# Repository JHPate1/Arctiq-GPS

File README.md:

# Arctiq-GPS
A mainboard PCB design for my custom handheld navigation device.
(first time making a PCB and it all looks good so far!)

## What does it do?
This might seem vague if you don't know much about the project, so I'll try to explain everything here, along with who I am and my background.

## Who I am
I'm Jyot Patel, a 14-year-old living in the United States. I recently moved from Canada, where I was raised my entire life (born in India though). I like tinkering and making software projects in my free time, though I never really used GitHub that often. Git CLI just wasn't for me.

## What is this project?
This is the core foundation of my handheld device. It contains the power circuitry and the main GPS module that handles everything. At the heart of it sits an RPI CM4 module, which controls everything and runs the main OS I plan on flashing to the SD card.

## Why did I take on such an ambitious project for my first PCB?
Honestly, it was kind of a bad idea for a first PCB, but I do have experience with real hardware. It was more of a motivational thing: when you want to give up, you realize how much you've already put into the project, and that pushes you to keep going. This was my 4th revision of the board, so as you can see, it took me a while to get here.

## The routing looks ugly
I can admit the routing is terrible, but I checked it for the specific purpose and this will work just fine. I wasn't planning on making a Mona Lisa on a PCB. I just needed a functional board that won't explode after 3 years.

## Known Errors

Any DRC or ERC errors are left on purpose, KiCad was being a pain in the butt during import and export. I couldn't connect some traces, and there are a few schematic/footprint mixups. Take the PCB as the source of truth only!!!
If you spot anything else, feel free to open an issue.

### Special Thanks!
Special thanks to Hack Club Stardance for motivating me on this project. Without your help, I wouldn't have done it!

Thanks to https://github.com/ShawnHymel/rpi-cm4-carrier-template for providing me with the CM4 Carrier template!

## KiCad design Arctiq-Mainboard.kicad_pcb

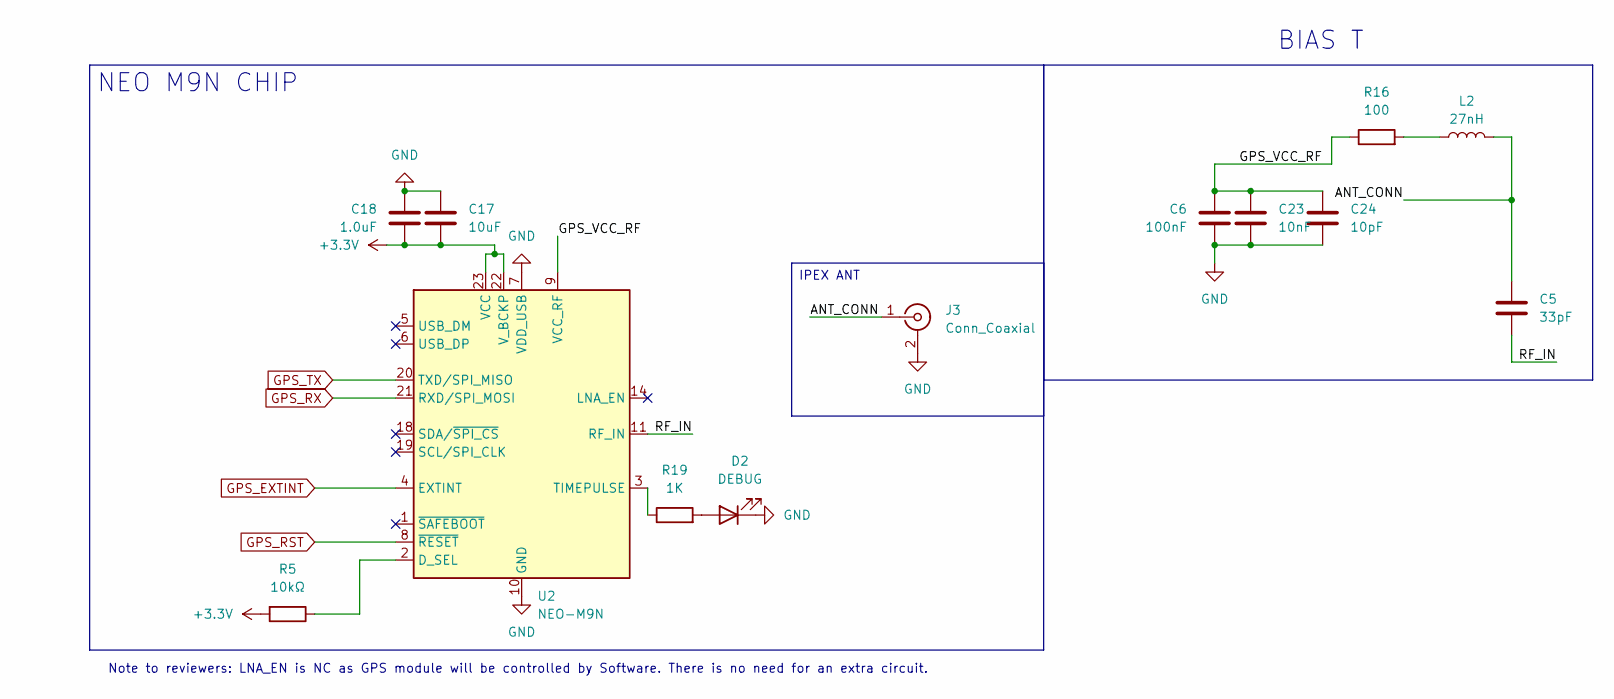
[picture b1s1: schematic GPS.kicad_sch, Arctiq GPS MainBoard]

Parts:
C5: 33pF; C_0603_1608Metric
C6: 100nF; C_0603_1608Metric
C17: 10uF; C_0603_1608Metric
C18: 1.0uF; C_0603_1608Metric
C23: 10nF; C_0603_1608Metric
C24: 10pF; C_0603_1608Metric
D2: DEBUG; LED_0402_1005Metric
J3: Conn_Coaxial; U.FL_Hirose_U.FL-R-SMT-1_Vertical
L2: 27nH; L_0402_1005Metric
R5: 10kΩ; R_0603_1608Metric
R16: 100; R_0603_1608Metric
R19: 1K; R_0603_1608Metric
U2: NEO-M9N; ublox_NEO

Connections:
+3.3V: C17.2, C18.2, R5.2, U2.22 (V_BCKP), U2.23 (VCC); also elsewhere on the board
/GPS Module/ANT_CONN: C5.2, J3.1 (In), L2.2
/GPS Module/GPS_VCC_RF: C6.2, C23.2, C24.2, R16.1, U2.9 (VCC_RF)
/GPS Module/RF_IN: C5.1, U2.11 (RF_IN)
GPS_EXTINT: U2.4 (EXTINT); also elsewhere on the board
GPS_RST: U2.8 (~RESET); also elsewhere on the board
GPS_RX: U2.21 (RXD/SPI_MOSI); also elsewhere on the board
GPS_TX: U2.20 (TXD/SPI_MISO); also elsewhere on the board
unnamed: D2.2 (A), R19.2
unnamed: L2.1, R16.2
unnamed: R5.1, U2.2 (D_SEL)
unnamed: R19.1, U2.3 (TIMEPULSE)

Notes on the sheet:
Note to reviewers: LNA_EN is NC as GPS module will be controlled by Software. There is no need for an extra circuit.
BIAS T
IPEX ANT
NEO M9N CHIP

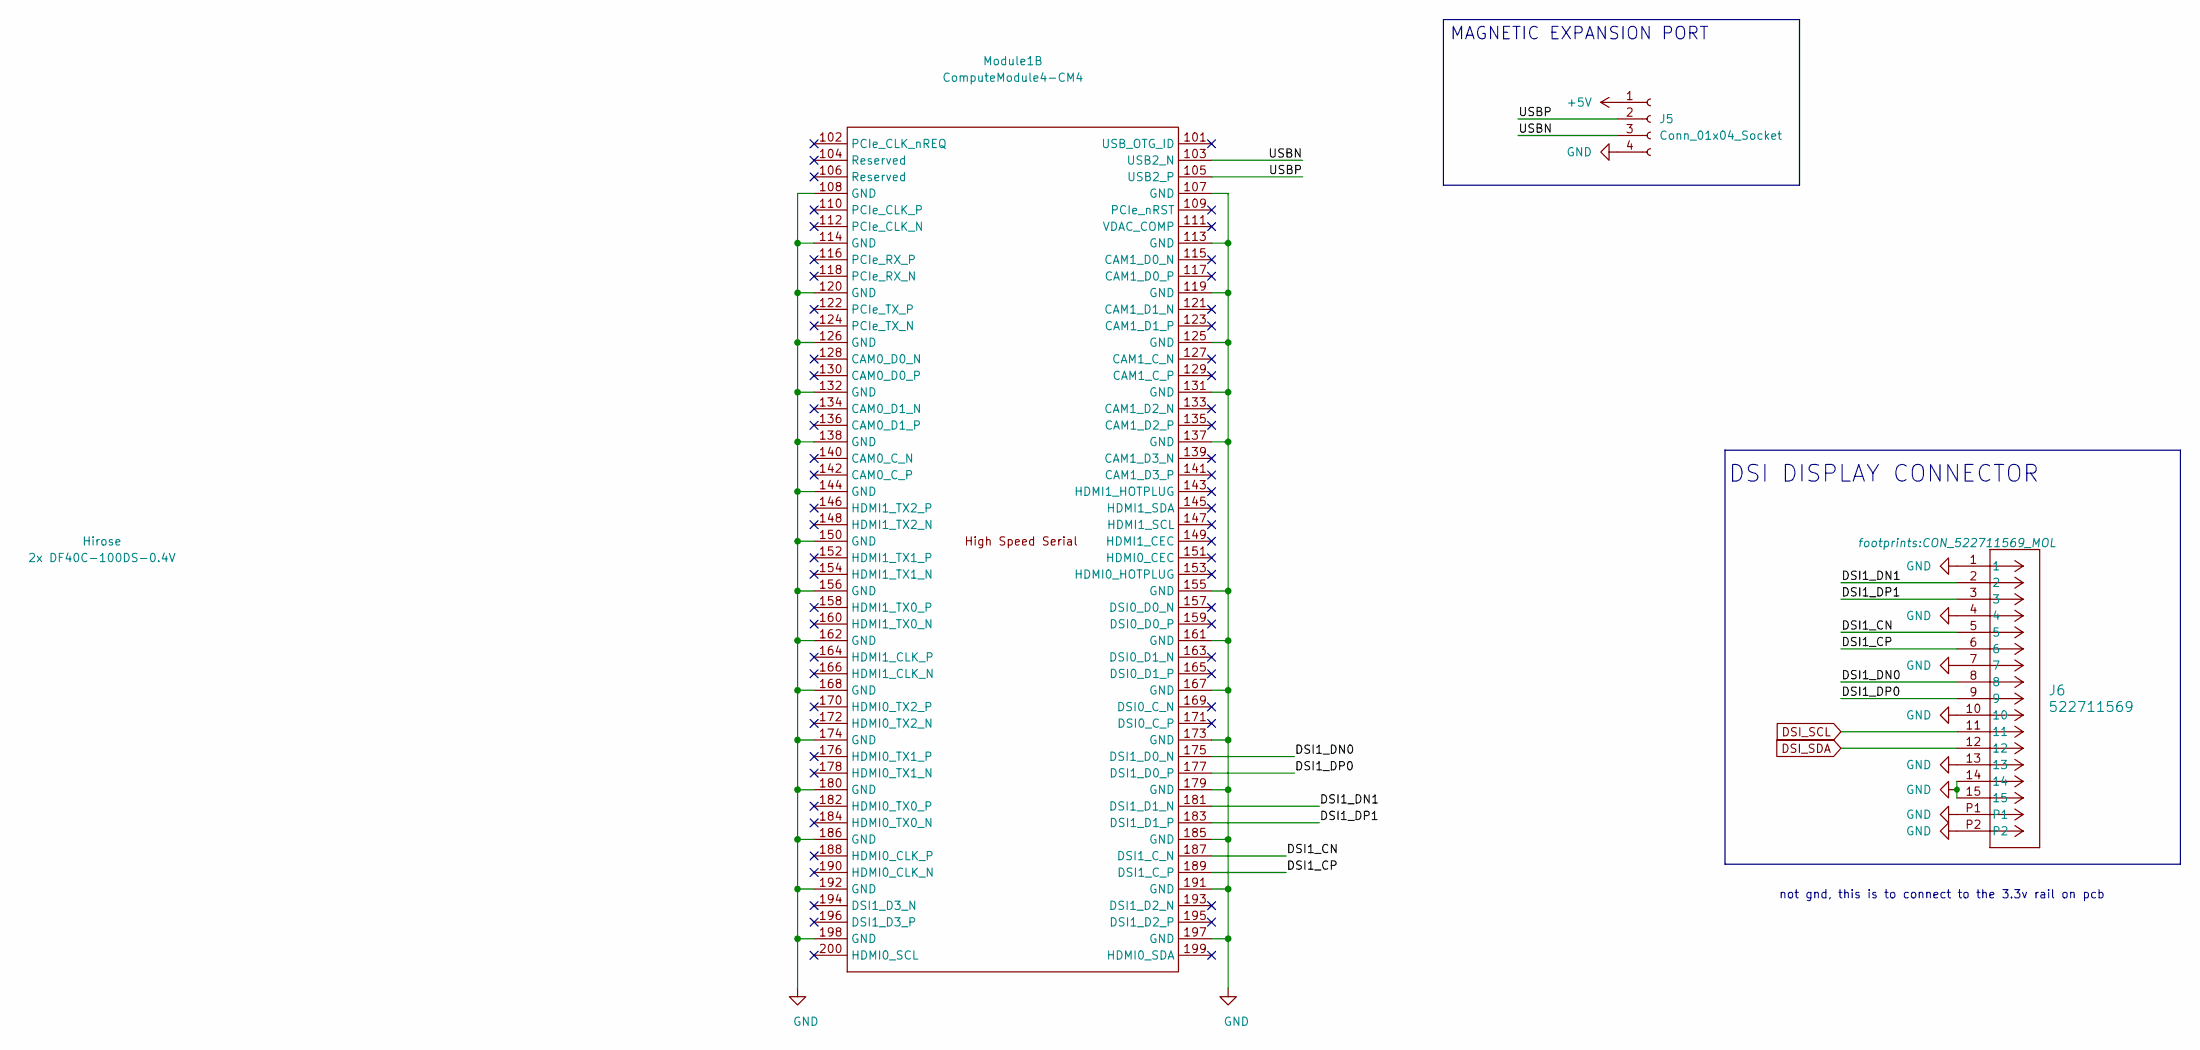
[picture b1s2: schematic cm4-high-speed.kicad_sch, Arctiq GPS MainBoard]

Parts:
J5: Conn_01x04_Socket; JST_NV_B04P-NV_1x04_P5.00mm_Vertical
J6: 522711569; CON_522711569_MOL
Module1: ComputeModule4-CM4; CONN100_DF40C-100DP-0.4V51_HIR; MPN 2x DF40C-100DS-0.4V; Digi-Key_PN 2x H11615CT-ND

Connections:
+5V: J5.1; also elsewhere on the board
/CM4 High Speed/DSI1_CN: J6.5, Module1.187 (DSI1_C_N)
/CM4 High Speed/DSI1_CP: J6.6, Module1.189 (DSI1_C_P)
/CM4 High Speed/DSI1_DN0: J6.8, Module1.175 (DSI1_D0_N)
/CM4 High Speed/DSI1_DN1: J6.2, Module1.181 (DSI1_D1_N)
/CM4 High Speed/DSI1_DP0: J6.9, Module1.177 (DSI1_D0_P)
/CM4 High Speed/DSI1_DP1: J6.3, Module1.183 (DSI1_D1_P)
/CM4 High Speed/USBN: J5.3, Module1.103 (USB2_N)
/CM4 High Speed/USBP: J5.2, Module1.105 (USB2_P)
DSI_SCL: J6.11; also elsewhere on the board
DSI_SDA: J6.12; also elsewhere on the board

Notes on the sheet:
not gnd, this is to connect to the 3.3v rail on pcb
DSI DISPLAY CONNECTOR
MAGNETIC EXPANSION PORT

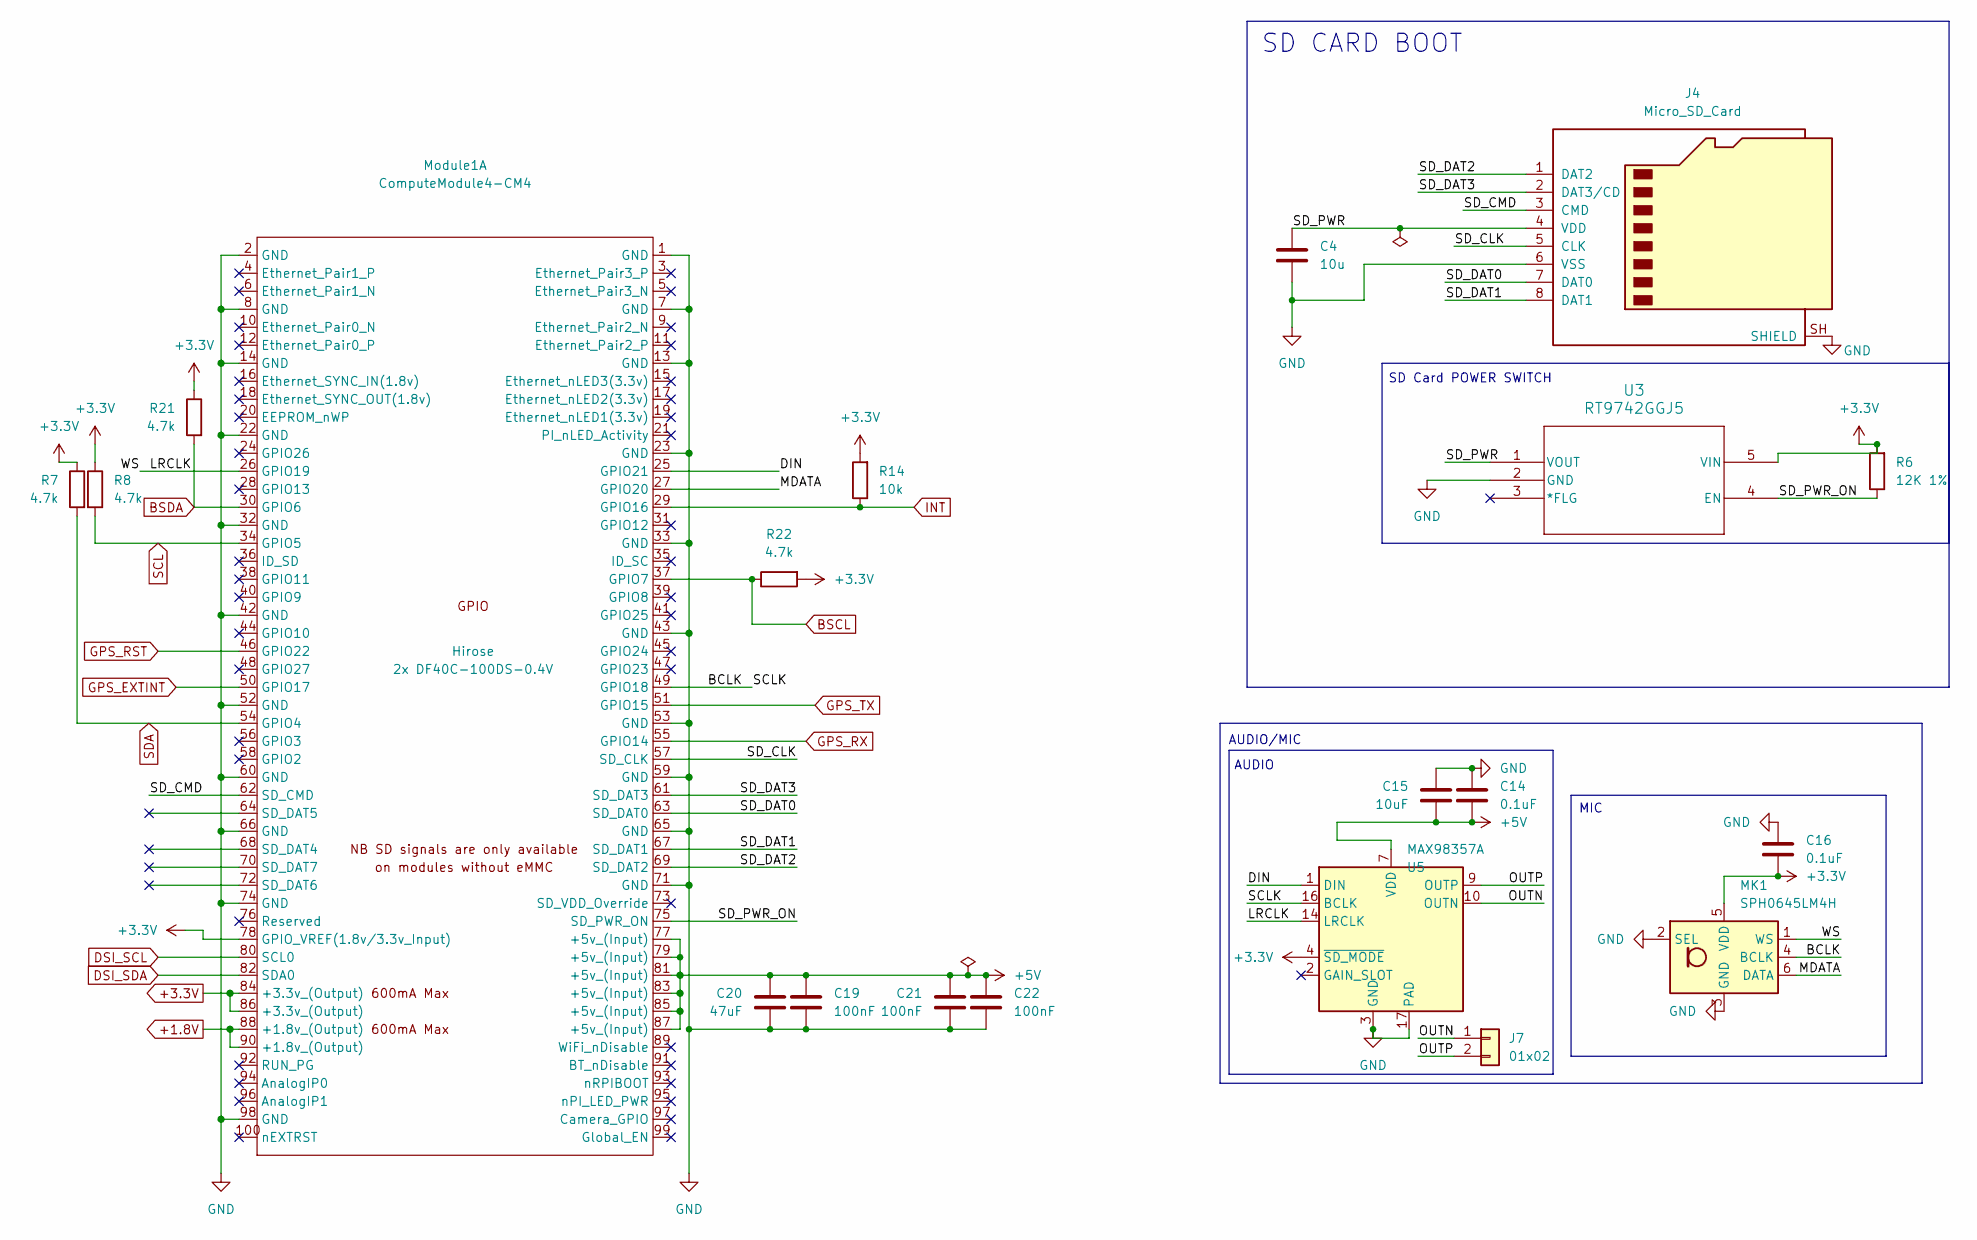
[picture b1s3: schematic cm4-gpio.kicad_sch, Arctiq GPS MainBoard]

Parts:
C4: 10u; C_0603_1608Metric
C14, C16: 0.1uF; C_0603_1608Metric
C15: 10uF; C_0603_1608Metric
C19, C21, C22: 100nF; C_0603_1608Metric
C20: 47uF; C_0603_1608Metric
J4: Micro_SD_Card; microSD_HC_Wuerth_693072010801
J7: 01x02; PinHeader_1x02_P2.54mm_Vertical
MK1: SPH0645LM4H; Knowles_SPH0645LM4H-6_3.5x2.65mm
Module1: ComputeModule4-CM4; CONN100_DF40C-100DP-0.4V51_HIR; MPN 2x DF40C-100DS-0.4V; Digi-Key_PN 2x H11615CT-ND
R6: 12K 1%; R_0603_1608Metric
R7, R8, R21, R22: 4.7k; R_0603_1608Metric
R14: 10k; R_0603_1608Metric
U3: RT9742GGJ5; TSOT-23-5_RIT
U5: MAX98357A; TQFN-16-1EP_3x3mm_P0.5mm_EP1.23x1.23mm

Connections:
+1.8V: Module1.88 (+1.8v_(Output)), Module1.90 (+1.8v_(Output))
+3.3V: C16.2, MK1.5 (VDD), Module1.78 (GPIO_VREF(1.8v/3.3v_Input)), Module1.84 (+3.3v_(Output)), Module1.86 (+3.3v_(Output)), R6.2, R7.1, R8.1, R14.2, R21.1, R22.2, U3.5 (VIN), U5.4 (~SD_MODE); also elsewhere on the board
+5V: C14.2, C15.2, C19.1, C20.2, C21.2, C22.1, Module1.77 (+5v_(Input)), Module1.79 (+5v_(Input)), Module1.81 (+5v_(Input)), Module1.83 (+5v_(Input)), Module1.85 (+5v_(Input)), Module1.87 (+5v_(Input)), U5.7 (VDD), U5.8 (VDD); also elsewhere on the board
/CM4 GPIO/BCLK: MK1.4 (BCLK), Module1.49 (GPIO18), U5.16 (BCLK)
/CM4 GPIO/DIN: Module1.25 (GPIO21), U5.1 (DIN)
/CM4 GPIO/LRCLK: MK1.1 (WS), Module1.26 (GPIO19), U5.14 (LRCLK)
/CM4 GPIO/MDATA: MK1.6 (DATA), Module1.27 (GPIO20)
/CM4 GPIO/OUTN: J7.1, U5.10 (OUTN)
/CM4 GPIO/OUTP: J7.2, U5.9 (OUTP)
/CM4 GPIO/SD_CLK: J4.5 (CLK), Module1.57 (SD_CLK)
/CM4 GPIO/SD_CMD: J4.3 (CMD), Module1.62 (SD_CMD)
/CM4 GPIO/SD_DAT0: J4.7 (DAT0), Module1.63 (SD_DAT0)
/CM4 GPIO/SD_DAT1: J4.8 (DAT1), Module1.67 (SD_DAT1)
/CM4 GPIO/SD_DAT2: J4.1 (DAT2), Module1.69 (SD_DAT2)
/CM4 GPIO/SD_DAT3: J4.2 (DAT3/CD), Module1.61 (SD_DAT3)
/CM4 GPIO/SD_PWR: C4.1, J4.4 (VDD), U3.1 (VOUT)
/CM4 GPIO/SD_PWR_ON: Module1.75 (SD_PWR_ON), R6.1, U3.4 (EN)
BSCL: Module1.37 (GPIO7), R22.1; also elsewhere on the board
BSDA: Module1.30 (GPIO6), R21.2; also elsewhere on the board
DSI_SCL: Module1.80 (SCL0); also elsewhere on the board
DSI_SDA: Module1.82 (SDA0); also elsewhere on the board
GPS_EXTINT: Module1.50 (GPIO17); also elsewhere on the board
GPS_RST: Module1.46 (GPIO22); also elsewhere on the board
GPS_RX: Module1.55 (GPIO14); also elsewhere on the board
GPS_TX: Module1.51 (GPIO15); also elsewhere on the board
INT: Module1.29 (GPIO16), R14.1; also elsewhere on the board
SCL: Module1.34 (GPIO5), R8.2; also elsewhere on the board
SDA: Module1.54 (GPIO4), R7.2; also elsewhere on the board

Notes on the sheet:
AUDIO
MIC
SD CARD BOOT
AUDIO/MIC
SD Card POWER SWITCH

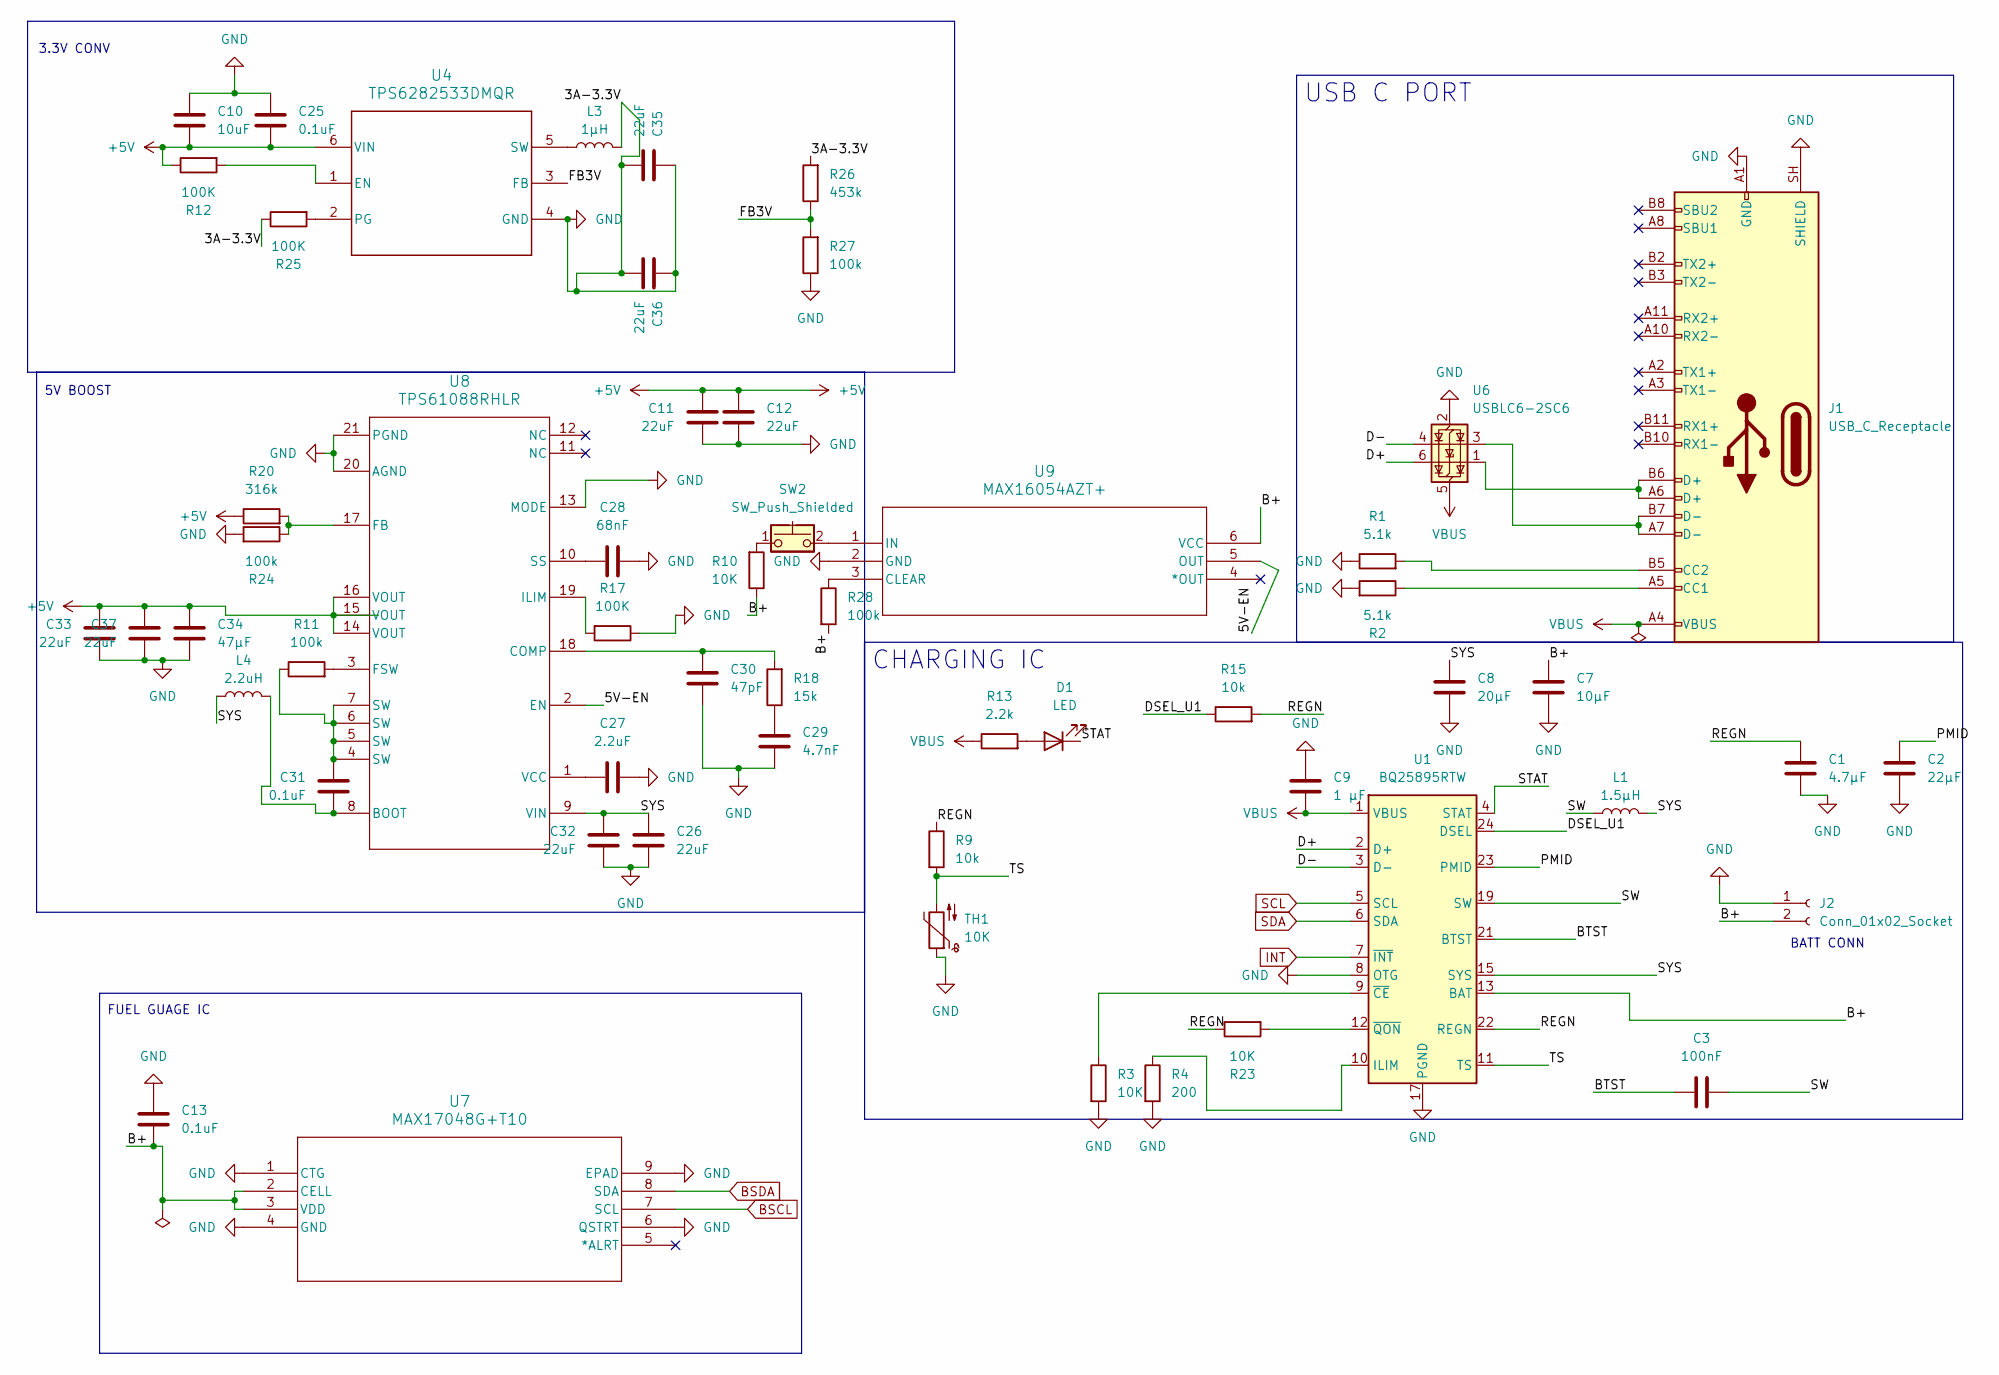
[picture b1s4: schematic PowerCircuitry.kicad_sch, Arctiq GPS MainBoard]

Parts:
C1: 4.7µF; C_0603_1608Metric
C2: 22µF; C_0603_1608Metric
C3: 100nF; C_0603_1608Metric
C7: 10µF; C_0603_1608Metric
C8: 20µF; C_0603_1608Metric
C9: 1 µF; C_0603_1608Metric
C10: 10uF; C_0603_1608Metric
C11, C12, C32, C33, C35, C36, C37: 22uF; C_0805_2012Metric
C13, C25, C31: 0.1uF; C_0603_1608Metric
C26: 22uF; C_0603_1608Metric
C27: 2.2uF; C_0603_1608Metric
C28: 68nF; C_0805_2012Metric
C29: 4.7nF; C_0603_1608Metric
C30: 47pF; C_0603_1608Metric
C34: 47µF; C_0603_1608Metric
D1: LED; LED_0402_1005Metric
J1: USB_C_Receptacle; USB_C_Receptacle_GCT_USB4085
J2: Conn_01x02_Socket; SolderWire-0.127sqmm_1x02_P3.7mm_D0.48mm_OD1mm
L1: 1.5µH; L_1210_3225Metric
L3: 1µH; L_0402_1005Metric
L4: 2.2uH; L_0603_1608Metric
R1, R2: 5.1k; R_0603_1608Metric
R3, R10, R23: 10K; R_0603_1608Metric
R4: 200; R_0603_1608Metric
R9, R15: 10k; R_0603_1608Metric
R11, R24, R27, R28: 100k; R_0603_1608Metric
R12, R17, R25: 100K; R_0603_1608Metric
R13: 2.2k; R_0603_1608Metric
R18: 15k; R_0603_1608Metric
R20: 316k; R_0603_1608Metric
R26: 453k; R_0603_1608Metric
SW2: SW_Push_Shielded; Panasonic_EVQPUJ_EVQPUA
TH1: 10K; R_0201_0603Metric
U1: BQ25895RTW; Texas_RTW_WQFN-24-1EP_4x4mm_P0.5mm_EP2.7x2.7mm_ThermalVias
U4: TPS6282533DMQR; DRL0006A
U6: USBLC6-2SC6; SOT-23-6
U7: MAX17048G+T10; 21-0168E_T822-3_MXM
U8: TPS61088RHLR; RHL0020A
U9: MAX16054AZT+; 21-0114C_MXM

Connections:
+5V: C10.2, C11.1, C12.1, C25.2, C33.2, C34.1, C37.2, R12.1, R20.1, U4.6 (VIN), U8.14 (VOUT), U8.15 (VOUT), U8.16 (VOUT); also elsewhere on the board
/Power Circuitry/5V-EN: U8.2 (EN), U9.5 (OUT)
/Power Circuitry/B+: C7.2, C13.2, J2.2, R10.1, R28.2, U1.13 (BAT), U1.14 (BAT), U7.2 (CELL), U7.3 (VDD), U9.6 (VCC)
/Power Circuitry/BTST: C3.2, U1.21 (BTST)
/Power Circuitry/D+: U1.2 (D+), U6.6 (I/O1)
/Power Circuitry/D-: U1.3 (D-), U6.4 (I/O2)
/Power Circuitry/DSEL_U1: R15.1, U1.24 (DSEL)
/Power Circuitry/FB3V: R26.1, R27.2, U4.3 (FB)
/Power Circuitry/PMID: C2.1, U1.23 (PMID)
/Power Circuitry/REGN: C1.2, R9.1, R15.2, R23.1, U1.22 (REGN)
/Power Circuitry/STAT: D1.1 (K), U1.4 (STAT)
/Power Circuitry/SW: C3.1, L1.1, U1.19 (SW), U1.20 (SW)
/Power Circuitry/SYS: C8.2, C26.1, C32.2, L1.2, L4.1, U1.15 (SYS), U1.16 (SYS), U8.9 (VIN)
/Power Circuitry/TS: R9.2, TH1.2, U1.11 (TS)
BSCL: U7.7 (SCL); also elsewhere on the board
BSDA: U7.8 (SDA); also elsewhere on the board
INT: U1.7 (~INT); also elsewhere on the board
unnamed: C29.1, R18.1
unnamed: C31.1, R11.1, U8.4 (SW), U8.5 (SW), U8.6 (SW), U8.7 (SW)
unnamed: D1.2 (A), R13.2
unnamed: J1.A5 (CC1), R2.1
unnamed: J1.B5 (CC2), R1.2
unnamed: J1.A6 (D+), J1.B6 (D+), U6.1 (I/O1)
unnamed: J1.A7 (D-), J1.B7 (D-), U6.3 (I/O2)
unnamed: R10.2, SW2.1
unnamed: R4.1, U1.10 (ILIM)
unnamed: R3.1, U1.9 (~CE)
unnamed: R23.2, U1.12 (~QON)
unnamed: R12.2, U4.1 (EN)
unnamed: R25.2, U4.2 (PG)
unnamed: L3.1, U4.5 (SW)
unnamed: C31.2, L4.2, U8.8 (BOOT)
unnamed: C30.1, R18.2, U8.18 (COMP)
unnamed: R20.2, R24.1, U8.17 (FB)
unnamed: R11.2, U8.3 (FSW)
unnamed: R17.2, U8.19 (ILIM)
unnamed: C28.1, U8.10 (SS)
unnamed: C27.1, U8.1 (VCC)
unnamed: R28.1, U9.3 (CLEAR)
unnamed: SW2.2, U9.1 (IN)
SCL: U1.5 (SCL); also elsewhere on the board
SDA: U1.6 (SDA); also elsewhere on the board
VBUS: C9.2, J1.A4 (VBUS), J1.A9 (VBUS), J1.B4 (VBUS), J1.B9 (VBUS), R13.1, U1.1 (VBUS), U6.5 (VBUS)

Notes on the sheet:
FUEL GUAGE IC
5V BOOST
3.3V CONV
BATT CONN
USB C PORT
CHARGING IC

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
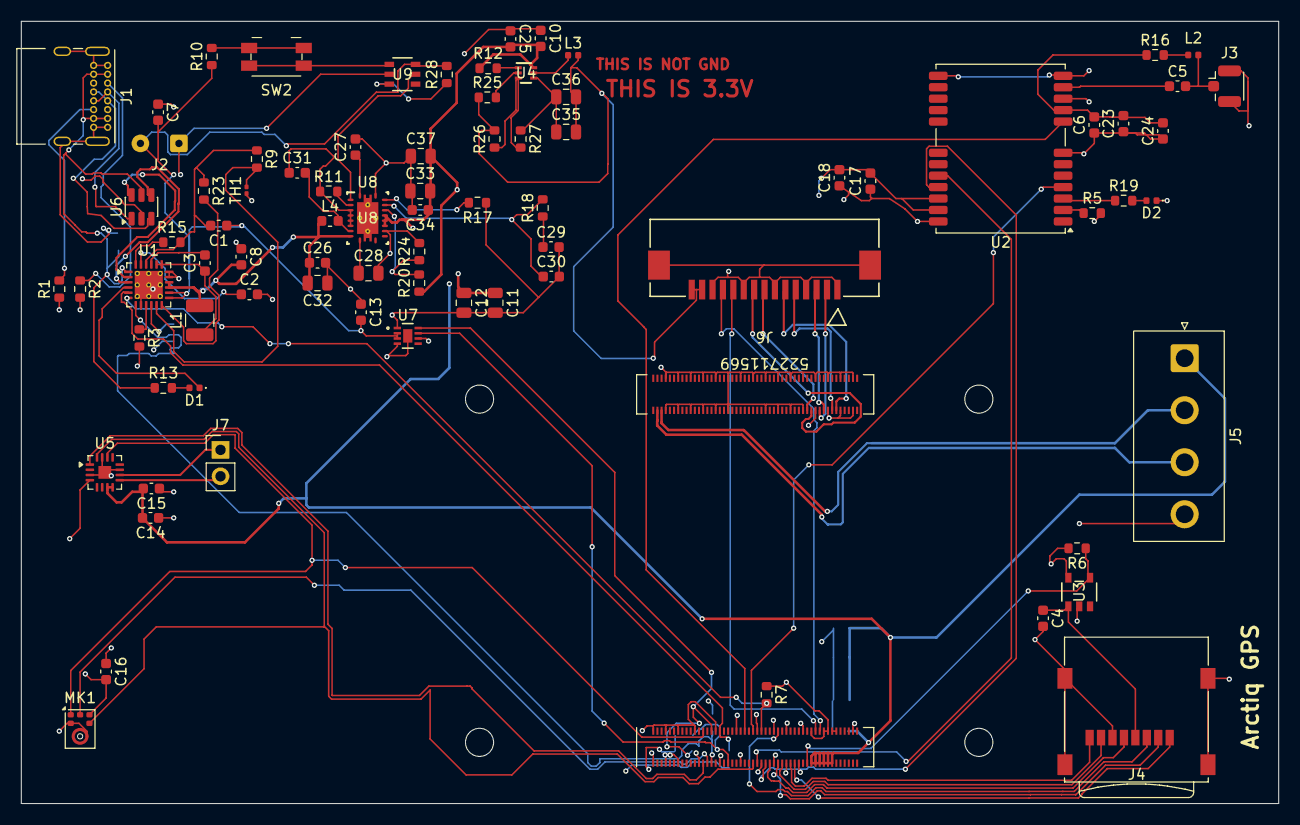
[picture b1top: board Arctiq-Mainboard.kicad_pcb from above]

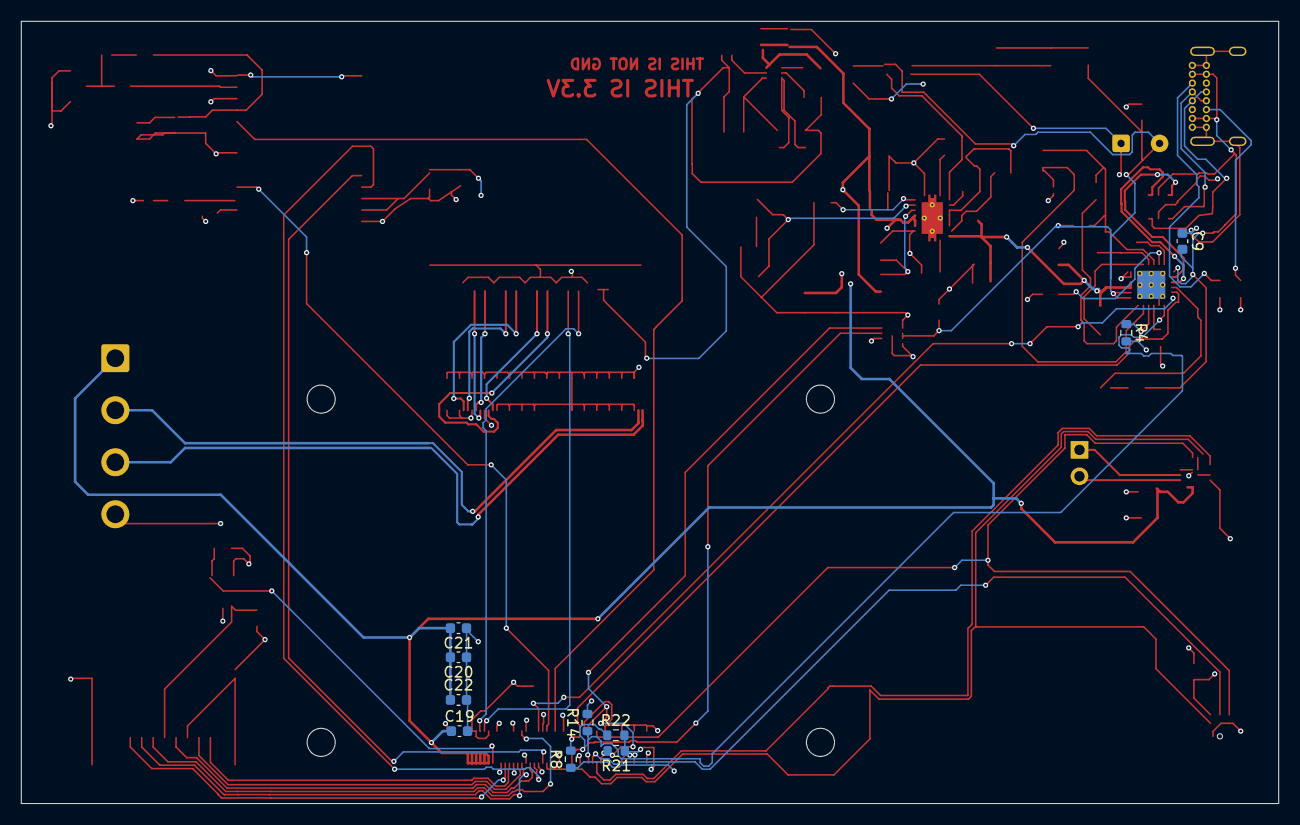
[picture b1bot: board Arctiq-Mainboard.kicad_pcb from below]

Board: 4 copper layers, 120.9 x 75.2 mm, 91 parts (10 on the bottom side), 81 nets.

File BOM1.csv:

#,Designator,Footprint,Qty,Designation,Recommended Spec,Digi-Key Part #,Unit Price,Ext Price
1,C1,C_0603_1608Metric,1,4.7µF,"4.7µF, X5R/X7R, ≥10V",Search Caps,$0.05,$0.05
2,C2,C_0603_1608Metric,1,22µF,"22µF, X5R/X7R, ≥10V",Search Caps,$0.05,$0.05
3,"C3, C6, C19, C21, C22",C_0603_1608Metric,5,100nF,"100nF, X7R, ≥10V",Search Caps,$0.05,$0.25
4,C4,C_0603_1608Metric,1,10µF,"10µF, X5R/X7R, ≥6.3V",Search Caps,$0.05,$0.05
5,C5,C_0603_1608Metric,1,33pF,"33pF, C0G/NP0, ≥25V",Search Caps,$0.05,$0.05
6,C7,C_0603_1608Metric,1,10µF,"10µF, X5R/X7R, ≥6.3V",Search Caps,$0.05,$0.05
7,C8,C_0603_1608Metric,1,20µF,"20µF, X5R/X7R, ≥6.3V",Search Caps,$0.05,$0.05
8,C9,C_0603_1608Metric,1,1µF,"1µF, X7R, ≥10V",Search Caps,$0.05,$0.05
9,"C10, C15, C17",C_0603_1608Metric,3,10µF,"10µF, X5R/X7R, ≥6.3V",Search Caps,$0.05,$0.15
10,"C11, C12, C32, C33, C35, C36, C37",C_0805_2012Metric,7,22µF,"22µF, X5R/X7R, ≥10V",Search Caps,$0.05,$0.35
11,"C13, C14, C16, C25, C31",C_0603_1608Metric,5,0.1µF,"0.1µF, X7R, ≥16V",Search Caps,$0.05,$0.25
12,C18,C_0603_1608Metric,1,1.0µF,"1.0µF, X7R, ≥6.3V",Search Caps,$0.05,$0.05
13,C20,C_0603_1608Metric,1,47µF,"47µF, X5R/X7R, ≥6.3V min; 10V preferred",Search Caps,$0.05,$0.05
14,C23,C_0603_1608Metric,1,10nF,"10nF, C0G/NP0, ≥25V",Search Caps,$0.05,$0.05
15,C24,C_0603_1608Metric,1,10pF,"10pF, C0G/NP0, ≥25V",Search Caps,$0.05,$0.05
16,C26,C_0603_1608Metric,1,22µF,"22µF, X5R/X7R, ≥6.3V",Search Caps,$0.05,$0.05
17,C27,C_0603_1608Metric,1,2.2µF,"2.2µF, X7R, ≥10V",Search Caps,$0.05,$0.05
18,C28,C_0805_2012Metric,1,68nF,"68nF, X7R, ≥10V",Search Caps,$0.05,$0.05
19,C29,C_0603_1608Metric,1,4.7nF,"4.7nF, X7R/C0G, ≥10V",Search Caps,$0.05,$0.05
20,C30,C_0603_1608Metric,1,47pF,"47pF, C0G/NP0, ≥25V",Search Caps,$0.05,$0.05
21,C34,C_0603_1608Metric,1,47µF,"47µF, X5R/X7R, ≥6.3V min; 10V preferred",Search Caps,$0.05,$0.05
22,D1,LED_0402_1005Metric,1,LED,,Search LEDs,$0.15,$0.15
23,D2,LED_0402_1005Metric,1,DEBUG,,Search LEDs,$0.15,$0.15
24,J1,USB_C_Receptacle_GCT_USB4085,1,USB-C Receptacle,,2073-USB4085-GF-ACT-ND,$0.89,$0.89
25,J2,SolderWire-0.127sqmm_1x02_P3.7mm,1,Conn_01x02_Socket,,Search Connectors,$0.50,$0.50
26,J3,U.FL_Hirose_U.FL-R-SMT-1_Vertical,1,U.FL Coaxial Connector,,H11891CT-ND,$1.29,$1.29
27,J4,microSD_HC_Wuerth_693072010801,1,microSD Card Holder,,732-693072010801-1-ND,$3.41,$3.41
28,J5,JST_NV_B04P-NV_1x04_P5.00mm_Vertical,1,Conn_01x04_Socket,,Search Connectors,$0.50,$0.50
29,J6,CON_522711569_MOL,1,522711569,,Search Connectors,$0.50,$0.50
30,J7,PinHeader_1x02_P2.54mm_Vertical,1,01x02 Pin Header,,Search Connectors,$0.50,$0.50
31,L1,L_1210_3225Metric,1,1.5µH,"1.5µH shielded power inductor, Isat ≥12A, low DCR",Search Inductors,$0.80,$0.80
32,L2,L_0402_1005Metric,1,27nH,27nH RF inductor/matching part,Search Inductors,$0.80,$0.80
33,L3,L_0402_1005Metric,1,1µH,"1µH power inductor, Isat ≥6A (0402 unsuitable for BQ25895 power stage)",Search Inductors,$0.80,$0.80
34,L4,L_0603_1608Metric,1,2.2µH,"2.2µH shielded power inductor, Isat ≥3A, low DCR",Search Inductors,$0.80,$0.80
35,MK1,Knowles_SPH0645LM4H-6_3.5x2.65mm,1,SPH0645LM4H,MEMS Microphone,6017-SPH0645LM4H-BCT-ND,$3.44,$3.44
36,Module1,Raspberry-Pi-4-Compute-Module,1,CM4 Compute Module,Raspberry Pi Compute Module 4 (SC0667),2648-SC0667-ND,$63.23,$63.23
37,"R1, R2",R_0603_1608Metric,2,5.1k,,Search Resistors,$0.01,$0.02
38,"R3, R10, R23",R_0603_1608Metric,3,10K,,Search Resistors,$0.01,$0.03
39,R4,R_0603_1608Metric,1,200,ILIM resistor,Search Resistors,$0.01,$0.01
40,R5,R_0603_1608Metric,1,10kΩ,,Search Resistors,$0.01,$0.01
41,R6,R_0603_1608Metric,1,12K 1%,,Search Resistors,$0.01,$0.01
42,"R7, R8, R21, R22",R_0603_1608Metric,4,4.7k,,Search Resistors,$0.01,$0.04
43,"R9, R14, R15",R_0603_1608Metric,3,10k,,Search Resistors,$0.01,$0.03
44,"R11, R24, R27, R28",R_0603_1608Metric,4,100k,,Search Resistors,$0.01,$0.04
45,"R12, R17, R25",R_0603_1608Metric,3,100K,,Search Resistors,$0.01,$0.03
46,R13,R_0603_1608Metric,1,2.2k,,Search Resistors,$0.01,$0.01
47,R16,R_0603_1608Metric,1,100,,Search Resistors,$0.01,$0.01
48,R18,R_0603_1608Metric,1,15k,,Search Resistors,$0.01,$0.01
49,R19,R_0603_1608Metric,1,1K,,Search Resistors,$0.01,$0.01
50,R20,R_0603_1608Metric,1,316k,,Search Resistors,$0.01,$0.01
51,R26,R_0603_1608Metric,1,453k,,Search Resistors,$0.01,$0.01
52,SW2,Panasonic_EVQPUJ_EVQPUA,1,Push Button Switch,Shielded tactile switch,P8029SCT-ND,$0.60,$0.60
53,TH1,R_0201_0603Metric,1,10K,Thermistor,Search Resistors,$0.01,$0.01
54,U1,Texas_RTW_WQFN-24-1EP_4x4mm,1,BQ25895RTW,Battery Buck-Boost Charger,296-44345-1-ND,$3.29,$3.29
55,U2,ublox_NEO,1,NEO-M9N,GNSS Receiver Module,672-NEO-M9N-00B-ND,$14.69,$14.69
56,U3,TSOT-23-5_RIT,1,RT9742GGJ5,Power Load Switch,1028-1436-1-ND,$0.92,$0.92
57,U4,DRL0006A,1,TPS6282533DMQR,Buck Converter 3.3V 2A,296-TPS6282533DMQRCT-ND,$1.25,$1.25
58,U5,TQFN-16-1EP_3x3mm,1,MAX98357A,Class D Audio Amplifier,MAX98357AETE+TCT-ND,$3.73,$3.73
59,U6,SOT-23-6,1,USBLC6-2SC6,USB ESD Protection,497-11882-1-ND,$0.67,$0.67
60,U7,21-0168E_T822-3_MXM,1,MAX17048G+T10,Fuel Gauge IC,MAX17048G+T10CT-ND,$3.62,$3.62
61,U8,RHL0020A,1,TPS61088RHLR,Boost Converter 10A,296-42129-1-ND,$2.74,$2.74
62,U9,21-0114C_MXM,1,MAX16054AZT+,Pushbutton On/Off Controller,MAX16054AZT+TCT-ND,$3.71,$3.71
63,NOB,4 PIN POGO MAG,1,4-Pin Pogo Magnetic Connector,,Amazon: B0GJPCX49H,$9.99,$9.99
64,NOB,"5 INCH DISPLAY, CAPACITIVE TOUCH, DSI",1,"5"" DSI Capacitive Touch Display",Waveshare 800×480,Amazon: B08H23KB1G,$46.00,$46.00
65,NOB,Active GNSS ANT,1,Active GNSS Antenna,,AliExpress,$8.00,$8.00
66,NOB,5000MAH Battery,2,5000mAh LiPo Battery,3.7V with JST PH2.0 connector,Amazon: B0GL1MH5YT,$13.00,$26.00
67,NOB,128GB SD,1,128GB microSD Card,Kingston Canvas Select Plus,Amazon: B0FCZTYSN6,$23.99,$23.99
68,NOB,ABS/RESIN ENCLOSURE,1,ABS/Resin Enclosure,Custom enclosure,PCBWAY (custom),$25.00,$25.00
69,NOB,SPEAKER,1,Speaker,,AliExpress,$5.00,$5.00
70,NOB,PCB + SHIPPING,1,PCB Fabrication & Shipping,PCB fabrication + component shipping,PCBWAY,$75.00,$75.00
,,TOTAL,100,,,,,$334.10

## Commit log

2026-06-24 Enhance README with project and personal information
    Added project details, personal background, and acknowledgments.
2026-06-24 Fix PCB image link in README.md
2026-06-24 Document known errors in PCB design
    Added a section for known errors in the PCB design.
2026-06-24 Add project journal entries detailing design challenges
    Documented the challenges and time spent on various aspects of the project, including RF issues, layout struggles, and validation efforts.
2026-06-24 Update journal with project time and issues
    Added new journal entries detailing time spent on project and issues encountered with the schematic.
